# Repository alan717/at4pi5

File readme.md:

aes132 for rasp 5 read/write board. 2024.04.28.

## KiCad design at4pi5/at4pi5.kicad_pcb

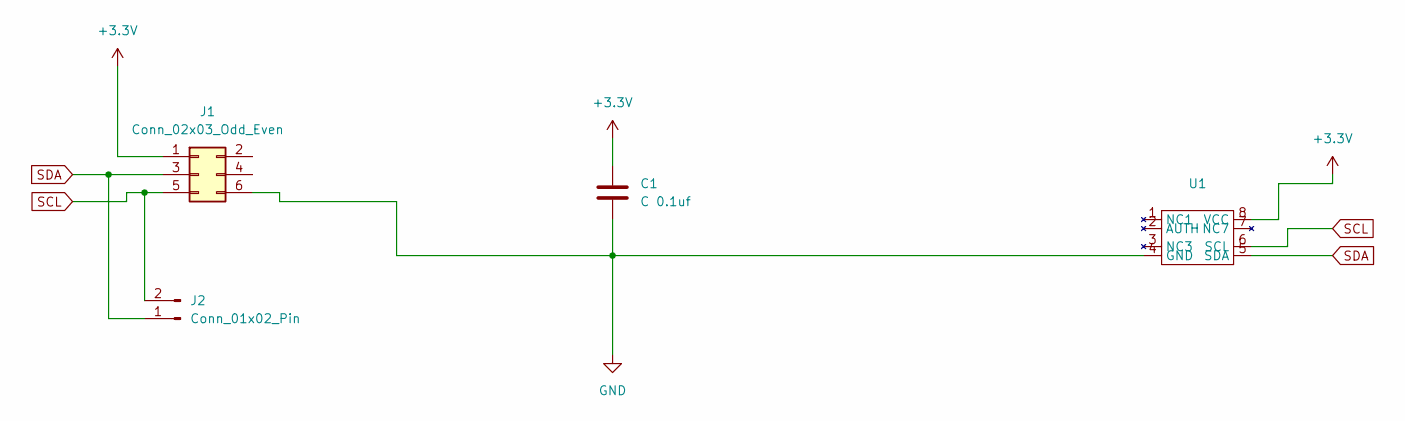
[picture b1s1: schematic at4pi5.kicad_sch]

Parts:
C1: C 0.1uf; C_0201_0603Metric_Pad0.64x0.40mm_HandSolder
J1: Conn_02x03_Odd_Even; PinHeader_2x03_P2.54mm_Vertical
J2: Conn_01x02_Pin; PinHeader_1x02_P2.54mm_Vertical
U1: SOIC-8_3.9x4.9mm_P1.27mm

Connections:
+3.3V: C1.1, J1.1, U1.8 (VCC)
GND: C1.2, J1.6, U1.4 (GND)
SCL: J1.5, J2.2, U1.6 (SCL)
SDA: J1.3, J2.1, U1.5 (SDA)

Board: 2 copper layers, 4 parts (0 on the bottom side), 4 nets, no tracks yet.

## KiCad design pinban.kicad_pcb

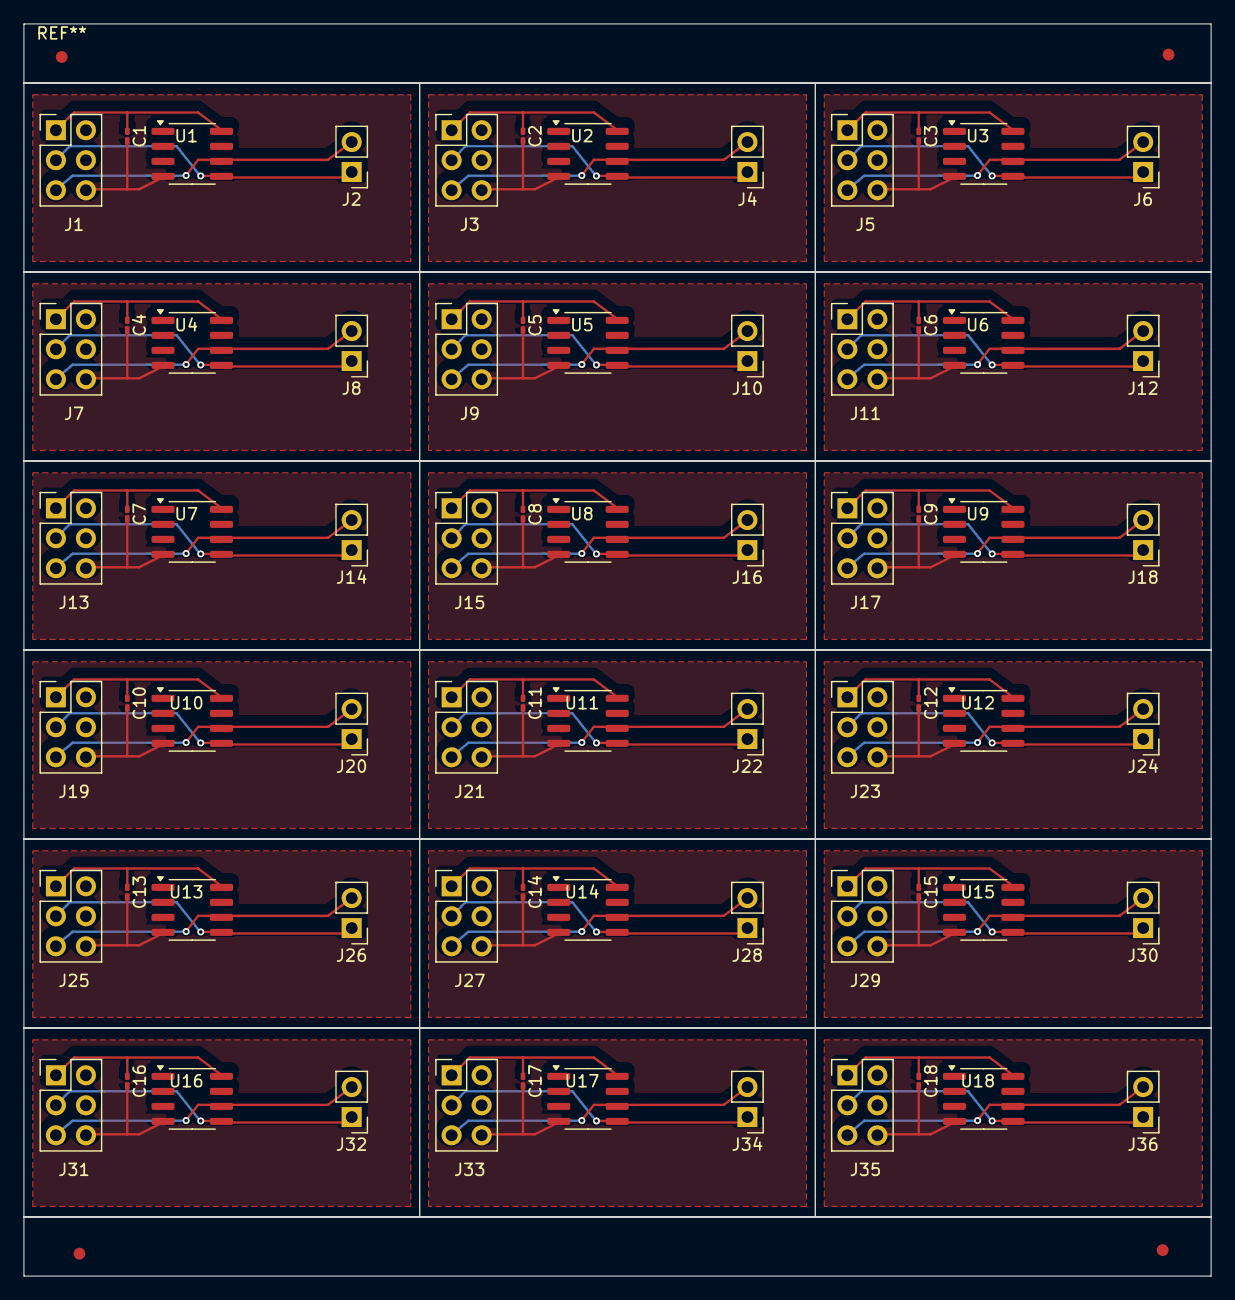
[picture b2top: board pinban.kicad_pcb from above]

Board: 2 copper layers, 100.5 x 106.0 mm, 72 parts (0 on the bottom side), 4 nets, no tracks yet.

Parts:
C1, C2, C3, C4, C5, C6, C7, C8, C9, C10, C11, C12, C13, C14, C15, C16, C17, C18: C 0.1uf; C_0201_0603Metric_Pad0.64x0.40mm_HandSolder
J1, J3, J5, J7, J9, J11, J13, J15, J17, J19, J21, J23, J25, J27, J29, J31, J33, J35: Conn_02x03_Odd_Even; PinHeader_2x03_P2.54mm_Vertical
J2, J4, J6, J8, J10, J12, J14, J16, J18, J20, J22, J24, J26, J28, J30, J32, J34, J36: Conn_01x02_Pin; PinHeader_1x02_P2.54mm_Vertical
U1, U2, U3, U4, U5, U6, U7, U8, U9, U10, U11, U12, U13, U14, U15, U16, U17, U18: SOIC-8_3.9x4.9mm_P1.27mm

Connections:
+3.3V: C1.1, C2.1, C3.1, C4.1, C5.1, C6.1, C7.1, C8.1, C9.1, C10.1, C11.1, C12.1, C13.1, C14.1, C15.1, C16.1, C17.1, C18.1, J1.1, J3.1, J5.1, J7.1, J9.1, J11.1, J13.1, J15.1, J17.1, J19.1, J21.1, J23.1, J25.1, J27.1, J29.1, J31.1, J33.1, J35.1, U1.8 (VCC), U2.8 (VCC), U3.8 (VCC), U4.8 (VCC), U5.8 (VCC), U6.8 (VCC), U7.8 (VCC), U8.8 (VCC), U9.8 (VCC), U10.8 (VCC), U11.8 (VCC), U12.8 (VCC), U13.8 (VCC), U14.8 (VCC), U15.8 (VCC), U16.8 (VCC), U17.8 (VCC), U18.8 (VCC)
GND: C1.2, C2.2, C3.2, C4.2, C5.2, C6.2, C7.2, C8.2, C9.2, C10.2, C11.2, C12.2, C13.2, C14.2, C15.2, C16.2, C17.2, C18.2, J1.6, J3.6, J5.6, J7.6, J9.6, J11.6, J13.6, J15.6, J17.6, J19.6, J21.6, J23.6, J25.6, J27.6, J29.6, J31.6, J33.6, J35.6, U1.4 (GND), U2.4 (GND), U3.4 (GND), U4.4 (GND), U5.4 (GND), U6.4 (GND), U7.4 (GND), U8.4 (GND), U9.4 (GND), U10.4 (GND), U11.4 (GND), U12.4 (GND), U13.4 (GND), U14.4 (GND), U15.4 (GND), U16.4 (GND), U17.4 (GND), U18.4 (GND)
SCL: J1.5, J2.2, J3.5, J4.2, J5.5, J6.2, J7.5, J8.2, J9.5, J10.2, J11.5, J12.2, J13.5, J14.2, J15.5, J16.2, J17.5, J18.2, J19.5, J20.2, J21.5, J22.2, J23.5, J24.2, J25.5, J26.2, J27.5, J28.2, J29.5, J30.2, J31.5, J32.2, J33.5, J34.2, J35.5, J36.2, U1.6 (SCL), U2.6 (SCL), U3.6 (SCL), U4.6 (SCL), U5.6 (SCL), U6.6 (SCL), U7.6 (SCL), U8.6 (SCL), U9.6 (SCL), U10.6 (SCL), U11.6 (SCL), U12.6 (SCL), U13.6 (SCL), U14.6 (SCL), U15.6 (SCL), U16.6 (SCL), U17.6 (SCL), U18.6 (SCL)
SDA: J1.3, J2.1, J3.3, J4.1, J5.3, J6.1, J7.3, J8.1, J9.3, J10.1, J11.3, J12.1, J13.3, J14.1, J15.3, J16.1, J17.3, J18.1, J19.3, J20.1, J21.3, J22.1, J23.3, J24.1, J25.3, J26.1, J27.3, J28.1, J29.3, J30.1, J31.3, J32.1, J33.3, J34.1, J35.3, J36.1, U1.5 (SDA), U2.5 (SDA), U3.5 (SDA), U4.5 (SDA), U5.5 (SDA), U6.5 (SDA), U7.5 (SDA), U8.5 (SDA), U9.5 (SDA), U10.5 (SDA), U11.5 (SDA), U12.5 (SDA), U13.5 (SDA), U14.5 (SDA), U15.5 (SDA), U16.5 (SDA), U17.5 (SDA), U18.5 (SDA)

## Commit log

2024-04-28 first add.
2024-04-28 add readme.
